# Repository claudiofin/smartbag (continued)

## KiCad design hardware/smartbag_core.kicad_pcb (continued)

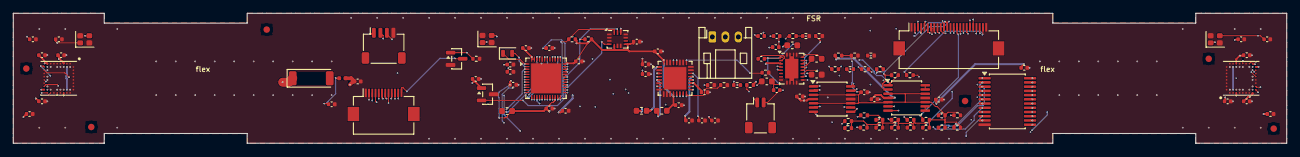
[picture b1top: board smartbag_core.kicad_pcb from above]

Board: 6 copper layers, 196.0 x 20.0 mm, 113 parts (0 on the bottom side), 100 nets.

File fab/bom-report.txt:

BOM vs footprints — measured, not asserted

  ok U1   NRF54L15-QFAA-R        QFN48      datasheet  48 pins / 6.0x6.0 mm   footprint  49 pins /   7.5x7.2 mm
  ok U2   A121-001-T&R           fcCSP50    datasheet  50 pins / 5.2x5.5 mm   footprint  50 pins /   5.7x6.0 mm
  ok U6   A121-001-T&R           fcCSP50    datasheet  50 pins / 5.2x5.5 mm   footprint  50 pins /   5.7x6.0 mm
  ok U3   NPM1300-QEAA-R7        QFN32      datasheet  32 pins / 5.0x5.0 mm   footprint  33 pins /   6.6x6.3 mm
  ok U4   BMI270                 LGA-14     datasheet  14 pins / 2.5x3.0 mm   footprint  14 pins /   3.8x3.3 mm
  ok U5   DRV5032FBDBZR          SOT-23-3   datasheet   3 pins / 2.92x2.37 mm   footprint   3 pins /   3.9x3.4 mm
  ok U11  BQ51013BRHLR           VQFN-20 (RHL) datasheet  20 pins / 4.5x3.5 mm   footprint  21 pins /   4.4x5.4 mm
  ok Q1   SI2302CDS-T1-GE3       SOT-23     datasheet   3 pins / 2.9x1.3 mm   footprint   3 pins /   3.9x3.4 mm   [pdf not archived]
  ok U7   CD74HC4067SM96         SSOP-24    datasheet  24 pins / 5.3x8.2 mm   footprint  24 pins /   9.4x8.9 mm
  ok U8   TLV9064IPWR            TSSOP-14   datasheet  14 pins / 4.4x5.0 mm   footprint  14 pins /   7.7x5.6 mm   [pdf not archived]
  ok U9   TLV9064IPWR            TSSOP-14   datasheet  14 pins / 4.4x5.0 mm   footprint  14 pins /   7.7x5.6 mm   [pdf not archived]
  ok Y1   ABM8-32.000MHZ-B2-T    SMD-2016-4 datasheet   4 pins / 2.0x1.6 mm   footprint   4 pins /   3.0x2.6 mm   [pdf not archived]
  ok Y4   ABS07-32.768KHZ-9-T    SMD-2012-2 datasheet   2 pins / 2.0x1.2 mm   footprint   2 pins /   3.0x2.2 mm   [pdf not archived]
  ok Y2   ABM8-24.000MHZ-B2-T    SMD-2016-4 datasheet   4 pins / 2.0x1.6 mm   footprint   4 pins /   3.0x2.6 mm   [pdf not archived]
  ok Y3   ABM8-24.000MHZ-B2-T    SMD-2016-4 datasheet   4 pins / 2.0x1.6 mm   footprint   4 pins /   3.0x2.6 mm   [pdf not archived]
  ok J1   FH12-12S-0.5SH(55)     FH12-12S   datasheet  12 pins / 10.4x4.3 mm   footprint  12 pins /  12.1x7.9 mm   [pdf not archived]
  ok J4   FH12-24S-0.5SH(55)     FH12-24S   datasheet  24 pins / 16.4x4.3 mm   footprint  24 pins /  18.1x7.9 mm   [pdf not archived]
  ok J2   S3B-PH-K-S(LF)(SN)     JST-PH-03  datasheet   3 pins / 7.9x4.5 mm   footprint   3 pins /   8.9x8.6 mm   [pdf not archived]
  ok J3   SM02B-SRSS-TB(LF)(SN)  JST-SH-02  datasheet   2 pins / 4.25x2.9 mm   footprint   2 pins /   5.8x6.6 mm   [pdf not archived]
  ok J5   SM04B-SRSS-TB(LF)(SN)  JST-SH-04  datasheet   4 pins / 6.25x2.9 mm   footprint   4 pins /   7.8x6.6 mm   [pdf not archived]
  ok AE1  2450AT43F0100E         SMD chip   datasheet   2 pins / 6.0x2.0 mm   footprint   2 pins /   7.4x2.7 mm   [pdf not archived]
  ok U10  VL53L1CXV0FY/1         LGA-12     datasheet  12 pins / 4.9x2.5 mm   footprint  12 pins /   5.5x3.1 mm
  ok J11  SM06B-SRSS-TB(LF)(SN)  JST-SH-06  datasheet   6 pins / 8.25x2.9 mm   footprint   6 pins /   9.8x6.6 mm   [pdf not archived]

  availability, as of 2026-08-30 — a snapshot, not a promise:
     U1   LCSC C42458750, $3.99/1, $2.72/100, out of stock 2026-08-30
     U2   distributor stock not verified
     U6   distributor stock not verified
     U3   LCSC C7501206, $1.75/1, $1.66/100, out of stock 2026-08-30
     U4   commodity, widely stocked
     U5   commodity, widely stocked
     U11  commodity
     Q1   commodity
     U7   commodity
     U8   commodity
     U9   commodity
     Y1   commodity
     Y4   commodity
     Y2   commodity
     Y3   commodity
     J1   commodity
     J4   commodity
     J2   commodity
     J3   commodity
     J5   commodity
     AE1  commodity
     U10  commodity
     J11  commodity

  86 passives in 29 distinct values, derived from the netlist:
     0402           0.3p C0G               x1   C11
     0402           0R                     x1   R12
     0402           1.2k 1%                x1   R11
     0402           1.5p NP0               x1   C6
     0402           100R 1%                x1   R21
     0402           100k 1%                x17  R13 R60 R61 R62 R63 R64 +11 more
     0402           100n X7R               x11  C4 C50 C51 C52 C61 C62 +5 more
     0402           10k 1%                 x4   R2 R22 R3 R5
     0402           10n X7R                x2   C82 C83
     0603           10u X5R 25V            x1   C88
     0402           10u X5R 6.3V           x3   C40 C41 C42
     0402           10u X6S 6.3V           x1   C3
     0402           1M 1%                  x1   R4
     0402           1k 1%                  x1   R6
     0402           1u X5R                 x13  C20 C21 C22 C23 C30 C31 +7 more
     0402           2.2n X7R               x1   C5
     0603           2.2u 1.2A              x2   L3 L4
     0402           2.2u X6T 2.5V          x2   C1 C2
     0402           2.7n                   x1   L2
     0402           220R 1%                x1   R20
     0603           220n C0G (Cs)          x1   C80
     0402           2n2 C0G (Cd)           x1   C81
     0402           4.7k 1%                x2   R7 R8
     0603           4.7u 120mA             x1   L1
     0603           470n X7R 25V           x2   C84 C85
     0402           47n X7R                x2   C86 C87
     0402           6.8k 1%                x1   R10
     0402           8.2k 1%                x6   R40 R41 R42 R43 R44 R45
     0402           8p NP0                 x4   C24 C25 C34 C35
⚠️ 2 things the design needs and the board has not got:

   - a tuned antenna match
     L2/C6/C11 are the chip vendor's reference values. A chip antenna matches against the ground plane around it, and this ground plane is not theirs. ⚠️ This one cannot be closed on paper: it wants a network analyser and one of the boards this BOM orders.

   - real sensor data
     every threshold in the firmware is either a datasheet figure or arithmetic over one, and ml/classify.py's accuracy is measured on rendered primitives. Whether a wallet can be told from a passport through four IR LEDs at 96x96 is a question the built thing answers and nothing else does.

wrote hardware/bom.csv

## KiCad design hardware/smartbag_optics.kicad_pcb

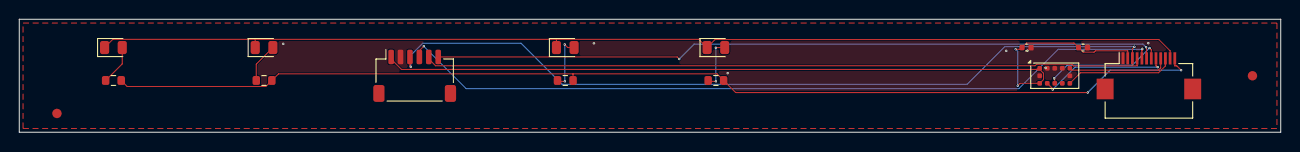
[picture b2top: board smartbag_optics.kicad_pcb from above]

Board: 2 copper layers, 134.0 x 12.0 mm, 15 parts (0 on the bottom side), 16 nets.

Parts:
C1: 100n X7R; C_0402_1005Metric
C2: 4u7 X5R 10V; C_0402_1005Metric
D1, D2, D3, D4: VSMY1850X01 850nm; LED_0805_2012Metric
FID1, FID2: fiducial; Fiducial_1mm_Mask2mm
J10: FFC to insert, 12 way; Hirose_FH12-12S-0.5SH_1x12-1MP_P0.50mm_Horizontal
J11: camera module, 6 way; JST_SH_SM06B-SRSS-TB_1x06-1MP_P1.00mm_Horizontal
R1, R2, R3, R4: 51R 1%; R_0603_1608Metric
U10: VL53L1X; ST_VL53L1x

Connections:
CS_CAM: J10.6, J11.6
GND: C1.2, C2.2, J10.1, J11.2, U10.2, U10.3, U10.4, U10.6, U10.12
I2C_SCL: J10.8, U10.10
I2C_SDA: J10.7, U10.9
IR_LED_K: J10.12, R1.2, R2.2, R3.2, R4.2
LED1_K: D1.2, R1.1
LED2_K: D2.2, R2.1
LED3_K: D3.2, R3.1
LED4_K: D4.2, R4.1
SPI_MISO: J10.5, J11.4
SPI_MOSI: J10.4, J11.5
SPI_SCK: J10.3, J11.3
TOF_INT: J10.10, U10.7
TOF_XSHUT: J10.9, U10.5
VDD_CAM: C1.1, C2.1, J10.2, J11.1, U10.1, U10.11
VSYS: D1.1, D2.1, D3.1, D4.1, J10.11

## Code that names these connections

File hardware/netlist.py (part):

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
# ─── U2 / U6: Acconeer A121, fcCSP50 ─────────────────────────────────────────
# ⛔ EVERY UNUSED PIN GOES TO GROUND BECAUSE THE DATASHEET SAYS SO, not because
# it is convenient: Analog0/1, CTRL, GPIO1..4 and PLL_RF_TEST are all listed as
# "connect to ground" or "must be connected to solid ground plane". RESET_N goes
# to VIO, also on instruction — it is not a reset the host drives.
_A121_GND = ("A3 A4 A5 A6 A7 A8 B2 B9 C1 C10 D2 D9 E1 E2 E9 F2 F9 G1 G10 "
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    return pins


U2_PINS = _a121("CS_RADAR_L", "RADAR_IRQ_L", "X24L_1", "X24L_2")
U6_PINS = _a121("CS_RADAR_R", "RADAR_IRQ_R", "X24R_1", "X24R_2")

# ─── U3: nPM1300-QEAA-R7, QFN32 ──────────────────────────────────────────────
# Pin table, nPM1300 product specification v1.1 page 150.
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    (4,  "PVDD", PWR_IN,   "VSYS"),
    (5,  "SW2", PASSIVE,   "SW2"),
    (6,  "PVSS2", PWR_IN,  "GND"),
    (7,  "GPIO0", OUT,     "PMIC_IRQ"),
    (8,  "GPIO1", PASSIVE, "GND"),
    (9,  "GPIO2", PASSIVE, "GND"),
    (10, "GPIO3", PASSIVE, "GND"),
    (11, "GPIO4", PASSIVE, "GND"),
    (12, "VDDIO", PWR_IN,  "VDD_3V3"),
    (13, "SDA", BIDI,      "I2C_SDA"),
    (14, "SCL", IN,        "I2C_SCL"),
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]

# ─── Crystals ────────────────────────────────────────────────────────────────
Y4_PINS = [(1, "XI", PASSIVE, "XTAL32K_1"), (2, "XO", PASSIVE, "XTAL32K_2")]
Y1_PINS = [(1, "XI", PASSIVE, "XTAL32M_1"), (2, "GND", PWR_IN, "GND"),
           (3, "XO", PASSIVE, "XTAL32M_2"), (4, "GND", PWR_IN, "GND")]
Y2_PINS = [(1, "XI", PASSIVE, "X24L_1"), (2, "GND", PWR_IN, "GND"),
           (3, "XO", PASSIVE, "X24L_2"), (4, "GND", PWR_IN, "GND")]
Y3_PINS = [(1, "XI", PASSIVE, "X24R_1"), (2, "GND", PWR_IN, "GND"),
           (3, "XO", PASSIVE, "X24R_2"), (4, "GND", PWR_IN, "GND")]

# ─── Connectors ──────────────────────────────────────────────────────────────
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# order you would choose if you were drawing a connector rather than plugging one
# in. The pack that is actually going to be bought — Jauch LP523450JU, whose
# harness is moulded onto a JST PHR-3 — is wired Pin 1 red (+), Pin 2 black (−),
# Pin 3 yellow (NTC). Plugging that into the old footprint puts the cell's
# NEGATIVE on the PMIC's thermistor input and the thermistor on ground.
#
# ⚠️ Nothing in this repository could have caught that. Every check here asks
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# and it sits between the coil and AC1; the other end of the winding lands on
# AC2 directly. Putting a capacitor in both legs would halve the series
# capacitance and move the tank off 100 kHz.
J3_PINS = [(1, "COIL_A", PASSIVE, "QI_COIL_A"),
           (2, "COIL_B", PASSIVE, "QI_AC2")]
J5_PINS = [(1, "VDD", PWR_IN, "VDD_3V3"), (2, "SWCLK", PASSIVE, "SWDCLK"),
           (3, "SWDIO", PASSIVE, "SWDIO"), (4, "GND", PWR_IN, "GND")]
# ⛔ TERMINAL 2 IS "NC", AND IT WAS TIED TO GROUND. The Johanson datasheet's
# terminal table says pin 1 is the feeding point and pin 2 is Not Connected —
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# directly and there is no matching network that recovers from that. This was in
# the netlist from the first version and nothing caught it, because a pad tied
# to ground is electrically unremarkable in every check the project runs.
AE1_PINS = [(1, "FEED", PASSIVE, "BLE_ANT"), (2, "NC", PASSIVE, "ANT_NC")]

_2 = lambda a, b: [(1, "1", PASSIVE, a), (2, "2", PASSIVE, b)]   # noqa: E731

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    # ⛔ C9 IS THE CAPACITOR THE COMMENT BELOW CLAIMED WAS ALREADY THERE. The
    # PLACEMENT table said "the QFN has VDD on all four sides, so there is a
    # capacitor on all four sides" and named C5 as the one on the top edge — and
    # C5 is 2.2 nF on DECRF, an internal regulator pin, not a supply. U1 pins 47
    # and 48 have had no decoupling since the first schematic. Nothing caught it
    # because a comment is not a check; tools/check.py now measures it.
    ("C9",  "100n X7R", "C_0402_1005Metric", "VDD_3V3", "GND", -19.0, -4.5),
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    # lives in the battery pack on J2 pin 2, where the temperature it reports is
    # the one the charge policy is actually about — a 0402 on this board
    # measures this board, twenty millimetres of foam away from the cell. And R1
    # pulled NTC up to VSYS: the nPM1300 biases that pin itself and measures
    # ratiometrically, so an external pull-up does not help the reading, it
    # corrupts it.
    #
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
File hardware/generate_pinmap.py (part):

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the schematic, restated in C, and every project that types it a second time
eventually has a board and an image that disagree about which pin is a chip
select. This one is generated: netlist.py says P2.10 carries CS_RADAR_R, so
sb_pinmap.h says P2.10 carries CS_RADAR_R, and there is no third place where a
human could put something else.

⭐ IT ALSO MAKES THE REASSIGNMENT SAFE. Routing moved the whole P2 block around —
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# enum and the right is netlist.py's net name; this dict is the only place the
# two vocabularies meet.
HAL_PINS = [
    ("SB_PIN_RADAR_EN", "RADAR_EN"),
    ("SB_PIN_RADAR_IRQ_L", "RADAR_IRQ_L"),
    ("SB_PIN_RADAR_IRQ_R", "RADAR_IRQ_R"),
    ("SB_PIN_TOF_XSHUT", "TOF_XSHUT"),
    ("SB_PIN_TOF_INT", "TOF_INT"),
    ("SB_PIN_IMU_INT1", "IMU_INT1"),
    ("SB_PIN_HALL", "HALL_OUT"),
    ("SB_PIN_PMIC_IRQ", "PMIC_IRQ"),
    ("SB_PIN_IR_LED_EN", "IR_LED_EN"),
]

CHIP_SELECTS = [("SB_CS_RADAR_L", "CS_RADAR_L"),
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         ' * peripheral that does not answer.',
         ' *',
         ' * ⚠️ Port and pin, not a Zephyr device: the devicetree in',
         ' * boards/smartbag.overlay is where these become gpio0/gpio1/gpio2',
         ' * handles. This header is what the overlay and the C agree on.',
         ' */',
         '#ifndef SB_PINMAP_H',
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    p_en, n_en = row("MUX_EN_N")
    L += ['};',
          f'#define SB_MUX_EN_PORT {p_en}',
          f'#define SB_MUX_EN_PIN  {n_en}      /* MUX_EN_N, active low */',
          '',
          '/* The six row amplifiers, as SAADC analog inputs. ⚠️ AINn is chosen by',
          ' * the pin, not by an index: on nRF54L each analog-capable pin maps to',
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&pinctrl {{
    spi00_default: spi00_default {{
        group1 {{
            psels = <NRF_PSEL(SPIM_SCK, {pins['SPI_SCK'][0]}, {pins['SPI_SCK'][1]})>,
                    <NRF_PSEL(SPIM_MOSI, {pins['SPI_MOSI'][0]}, {pins['SPI_MOSI'][1]})>,
                    <NRF_PSEL(SPIM_MISO, {pins['SPI_MISO'][0]}, {pins['SPI_MISO'][1]})>;
        }};
    }};

    spi00_sleep: spi00_sleep {{
        group1 {{
            psels = <NRF_PSEL(SPIM_SCK, {pins['SPI_SCK'][0]}, {pins['SPI_SCK'][1]})>,
                    <NRF_PSEL(SPIM_MOSI, {pins['SPI_MOSI'][0]}, {pins['SPI_MOSI'][1]})>,
                    <NRF_PSEL(SPIM_MISO, {pins['SPI_MISO'][0]}, {pins['SPI_MISO'][1]})>;
            low-power-enable;
        }};
    }};

    i2c21_default: i2c21_default {{
        group1 {{
            psels = <NRF_PSEL(TWIM_SDA, {pins['I2C_SDA'][0]}, {pins['I2C_SDA'][1]})>,
                    <NRF_PSEL(TWIM_SCL, {pins['I2C_SCL'][0]}, {pins['I2C_SCL'][1]})>;
            bias-pull-up;
        }};
    }};

    i2c21_sleep: i2c21_sleep {{
        group1 {{
            psels = <NRF_PSEL(TWIM_SDA, {pins['I2C_SDA'][0]}, {pins['I2C_SDA'][1]})>,
                    <NRF_PSEL(TWIM_SCL, {pins['I2C_SCL'][0]}, {pins['I2C_SCL'][1]})>;
            low-power-enable;
        }};
    }};
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    imu@68 {{
        compatible = "bosch,bmi270";
        reg = <0x68>;
        irq-gpios = <{gp('IMU_INT1')}>;
    }};

    tof@29 {{
        compatible = "st,vl53l1x";
        reg = <0x29>;
        xshut-gpios = <{gp('TOF_XSHUT')}>;
        int-gpios = <{gp('TOF_INT')}>;
    }};
}};

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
